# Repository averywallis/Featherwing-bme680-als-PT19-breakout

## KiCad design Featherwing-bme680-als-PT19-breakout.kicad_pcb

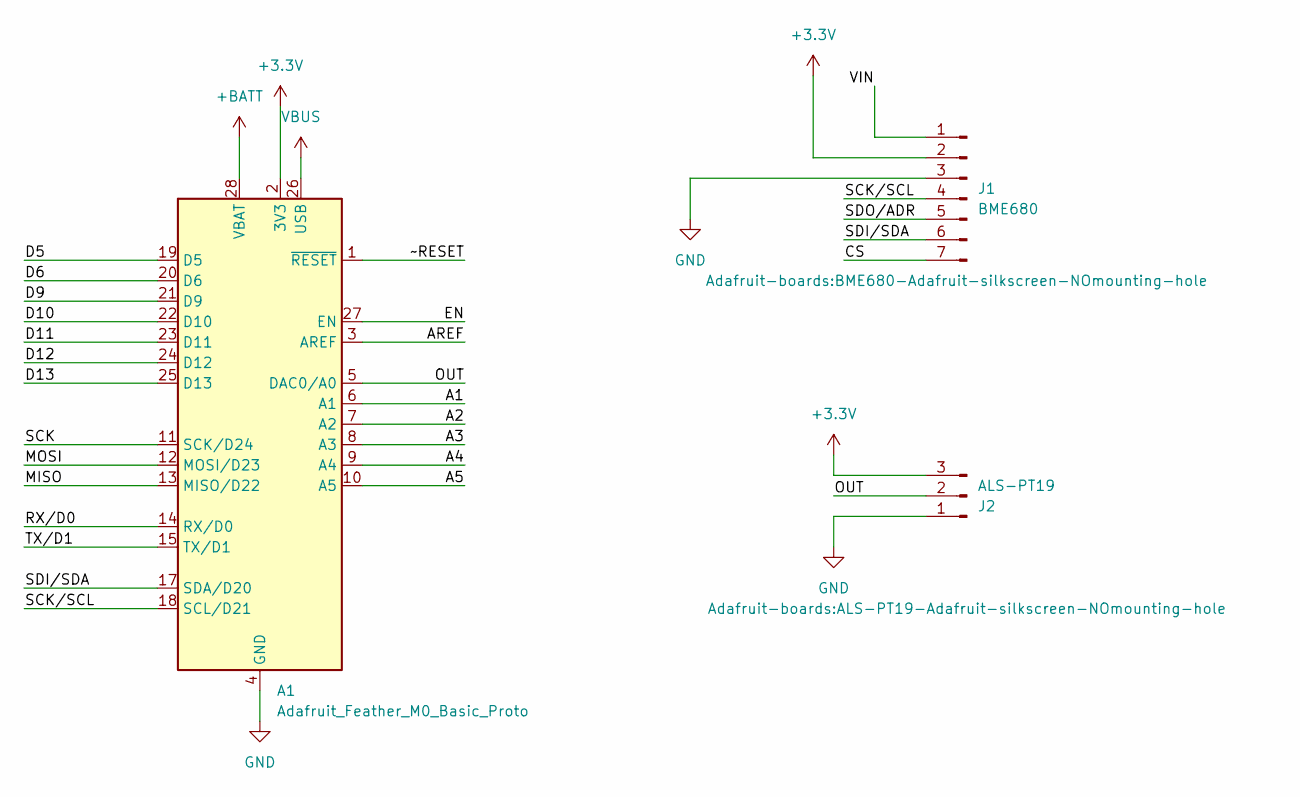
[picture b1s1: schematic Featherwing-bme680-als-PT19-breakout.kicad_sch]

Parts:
A1: Adafruit_Feather_M0_Basic_Proto; Adafruit_Feather
J1: BME680; BME680-Adafruit-silkscreen-NOmounting-hole
J2: ALS-PT19; ALS-PT19-Adafruit-silkscreen-NOmounting-hole

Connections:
+3V3: A1.2 (3V3), J1.2, J2.3
+BATT: A1.28 (VBAT)
/A1: A1.6 (A1)
/A2: A1.7 (A2)
/A3: A1.8 (A3)
/A4: A1.9 (A4)
/A5: A1.10 (A5)
/AREF: A1.3 (AREF)
/CS: J1.7
/D5: A1.19 (D5)
/D6: A1.20 (D6)
/D9: A1.21 (D9)
/D10: A1.22 (D10)
/D11: A1.23 (D11)
/D12: A1.24 (D12)
/D13: A1.25 (D13)
/EN: A1.27 (EN)
/MISO: A1.13 (MISO/D22)
/MOSI: A1.12 (MOSI/D23)
/OUT: A1.5 (DAC0/A0), J2.2
/RX/D0: A1.14 (RX/D0)
/SCK: A1.11 (SCK/D24)
/SCK/SCL: A1.18 (SCL/D21), J1.4
/SDI/SDA: A1.17 (SDA/D20), J1.6
/SDO/ADR: J1.5
/TX/D1: A1.15 (TX/D1)
/VIN: J1.1
/~RESET: A1.1 (~RESET)
GND: A1.4 (GND), A1.16 (GND), J1.3, J2.1
VBUS: A1.26 (USB)

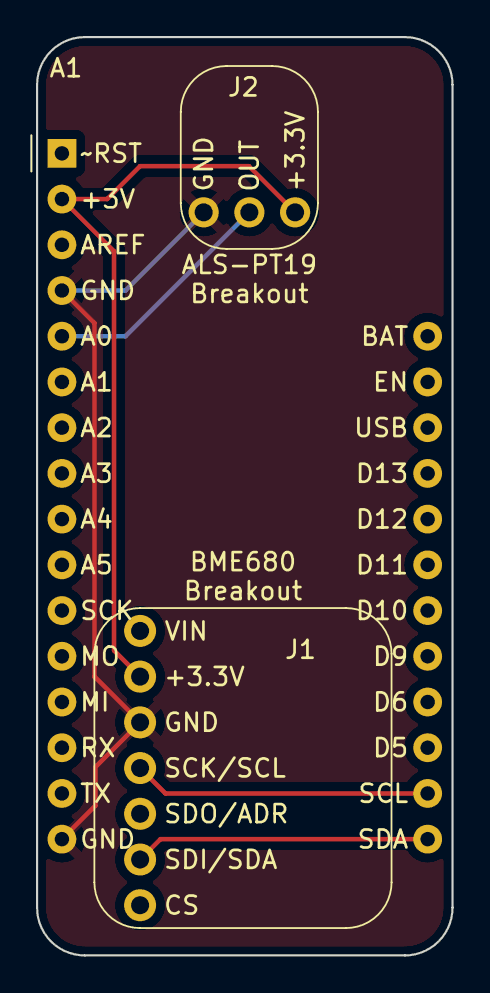
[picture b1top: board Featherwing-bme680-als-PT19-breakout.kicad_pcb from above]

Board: 2 copper layers, 23.1 x 51.0 mm, 3 parts (0 on the bottom side), 5 nets.

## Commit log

2022-01-29 Delete LICENSE
    Change to GPL
2022-01-29 Create LICENSE
